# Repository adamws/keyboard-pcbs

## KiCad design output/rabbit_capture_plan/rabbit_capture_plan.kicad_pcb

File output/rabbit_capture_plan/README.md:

## rabbit_capture_plan/rabbit_capture_plan

[layout](rabbit_capture_plan-kle.json) - [PCB](rabbit_capture_plan.kicad_pcb)

{:loading="lazy"}

[Open in keyboard-layout-editor](http://www.keyboard-layout-editor.com/##@@_x:0.66&y:1.45&c=#777777;&=0,0&_c=#cccccc;&=0,1&_x:11.66;&=5,4&=5,5&=5,6&_c=#aaaaaa;&=5,7;&@_x:0.53&w:1.5;&=1,0&_c=#cccccc;&=1,1&_x:10.94;&=6,4&=6,5&=6,6&_x:0.37&c=#777777&w:1.25&h:2&w2:1.5&h2:1&x2:-0.25;&=6,7%0A%0A%0A0,0;&@_x:0.39&c=#aaaaaa&w:1.75;&=2,0&_c=#cccccc;&=2,1&_x:11.2;&=7,4&=7,5&=7,6%0A%0A%0A0,0;&@_x:0.25&c=#aaaaaa&w:2.25;&=3,0&_c=#cccccc;&=3,1&_x:10.47;&=8,4&=8,5&_c=#aaaaaa&w:1.75;&=8,6%0A%0A%0A1,0;&@_x:18&y:-0.7&c=#cccccc;&=9,0;&@_x:0.5&y:-0.3&c=#aaaaaa&w:1.25;&=4,0&_w:1.25;&=4,1;&@_x:17&y:-0.7&c=#cccccc;&=9,3&=9,4&=9,5;&@_r:8&x:2.97&y:-5.82;&=0,2&=0,3&=0,4&=0,5&=0,6;&@_x:3.47;&=1,2&=1,3&=1,4&=1,5&=1,6;&@_x:3.72;&=2,2&=2,3&=2,4&=2,5&=2,6;&@_x:4.22;&=3,2&=3,3&=3,4&=3,5;&@_x:4.72;&=4,2&_w:2;&=4,3&=4,4;&@_r:-8&x:9.87&y:-2.58;&=5,0&=5,1&=5,2&=5,3;&@_x:9.37;&=6,0&=6,1&=6,2&=6,3;&@_x:9.62;&=7,0&=7,1&=7,2&=7,3;&@_x:9.12;&=8,0&=8,1&=8,2&=8,3;&@_x:9.6&w:2.75;&=9,1&=9,2;&@_r:0&x:21.47&y:-5.9&c=#aaaaaa&w:1.5;&=6,7%0A%0A%0A0,1;&@_x:20.84&c=#777777&w:2.25;&=7,6%0A%0A%0A0,1;&@_x:20.72&c=#cccccc;&=8,6%0A%0A%0A1,1&=8,7%0A%0A%0A1,1)

{:loading="lazy"}

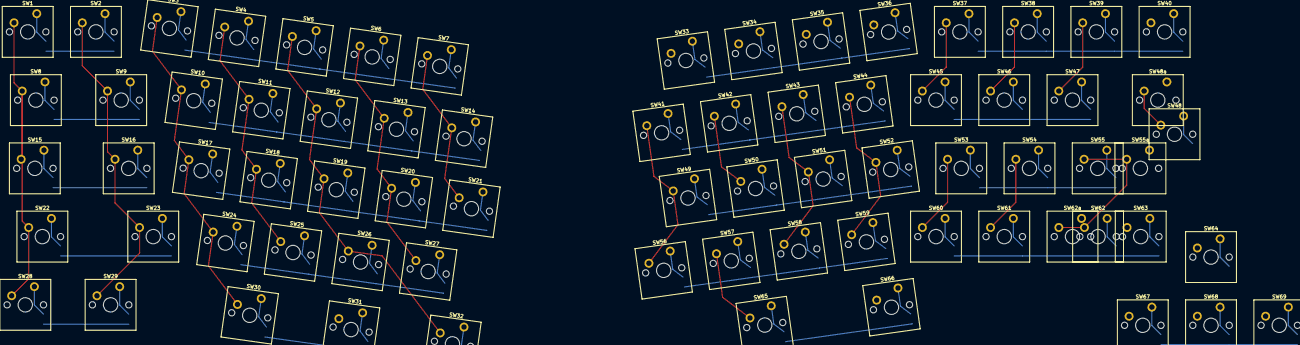
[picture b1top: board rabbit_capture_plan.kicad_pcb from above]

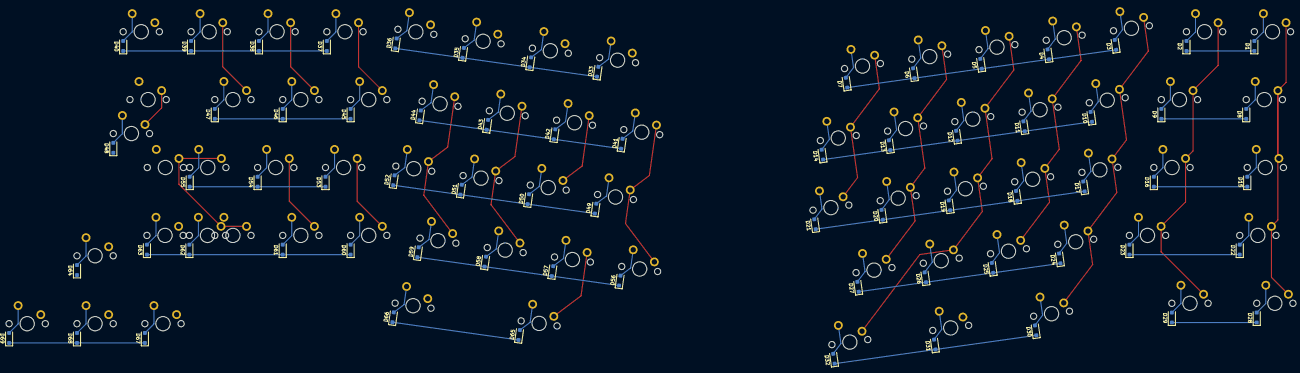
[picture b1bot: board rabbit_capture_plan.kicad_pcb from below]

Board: 2 copper layers, 141 parts (69 on the bottom side), 87 nets.

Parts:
D1, D2, D3, D4, D5, D6, D7, D8, D9, D10, D11, D12, D13, D14, D15, D16, D17, D18, D19, D20, D21, D22, D23, D24, D25, D26, D27, D28, D29, D30, D31, D32, D33, D34, D35, D36, D37, D38, D39, D40, D41, D42, D43, D44, D45, D46, D47, D48, D49, D50, D51, D52, D53, D54, D55, D56, D57, D58, D59, D60, D61, D62, D63, D64, D65, D66, D67, D68, D69: D_SOD-123F
SW1, SW2, SW3, SW4, SW5, SW6, SW7, SW8, SW9, SW10, SW11, SW12, SW13, SW14, SW15, SW16, SW17, SW18, SW19, SW20, SW21, SW22, SW23, SW24, SW25, SW26, SW27, SW28, SW29, SW30, SW31, SW32, SW33, SW34, SW35, SW36, SW37, SW38, SW39, SW40, SW41, SW42, SW43, SW44, SW45, SW46, SW47, SW48, SW48a, SW49, SW50, SW51, SW52, SW53, SW54, SW55, SW55a, SW56, SW57, SW58, SW59, SW60, SW61, SW62, SW62a, SW63, SW64, SW65, SW66, SW67, SW68, SW69: SW_Cherry_MX_PCB_1.00u

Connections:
COL0: SW1.1, SW8.1, SW15.1, SW22.1, SW28.1, SW33.1, SW41.1, SW49.1, SW56.1, SW64.1
COL1: SW2.1, SW9.1, SW16.1, SW23.1, SW29.1, SW34.1, SW42.1, SW50.1, SW57.1, SW65.1
COL2: SW3.1, SW10.1, SW17.1, SW24.1, SW30.1, SW35.1, SW43.1, SW51.1, SW58.1, SW66.1
COL3: SW4.1, SW11.1, SW18.1, SW25.1, SW31.1, SW36.1, SW44.1, SW52.1, SW59.1, SW67.1
COL4: SW5.1, SW12.1, SW19.1, SW26.1, SW32.1, SW37.1, SW45.1, SW53.1, SW60.1, SW68.1
COL5: SW6.1, SW13.1, SW20.1, SW27.1, SW38.1, SW46.1, SW54.1, SW61.1, SW69.1
COL6: SW7.1, SW14.1, SW21.1, SW39.1, SW47.1, SW55.1, SW55a.1, SW62.1, SW62a.1
COL7: SW40.1, SW48.1, SW48a.1, SW63.1
unnamed: D1.2, SW1.2
unnamed: D2.2, SW2.2
unnamed: D3.2, SW3.2
unnamed: D4.2, SW4.2
unnamed: D5.2, SW5.2
unnamed: D6.2, SW6.2
unnamed: D7.2, SW7.2
unnamed: D8.2, SW8.2
unnamed: D9.2, SW9.2
unnamed: D10.2, SW10.2
unnamed: D11.2, SW11.2
unnamed: D12.2, SW12.2
unnamed: D13.2, SW13.2
unnamed: D14.2, SW14.2
unnamed: D15.2, SW15.2
unnamed: D16.2, SW16.2
unnamed: D17.2, SW17.2
unnamed: D18.2, SW18.2
unnamed: D19.2, SW19.2
unnamed: D20.2, SW20.2
unnamed: D21.2, SW21.2
unnamed: D22.2, SW22.2
unnamed: D23.2, SW23.2
unnamed: D24.2, SW24.2
unnamed: D25.2, SW25.2
unnamed: D26.2, SW26.2
unnamed: D27.2, SW27.2
unnamed: D28.2, SW28.2
unnamed: D29.2, SW29.2
unnamed: D30.2, SW30.2
unnamed: D31.2, SW31.2
unnamed: D32.2, SW32.2
unnamed: D33.2, SW33.2
unnamed: D34.2, SW34.2
unnamed: D35.2, SW35.2
unnamed: D36.2, SW36.2
unnamed: D37.2, SW37.2
unnamed: D38.2, SW38.2
unnamed: D39.2, SW39.2
unnamed: D40.2, SW40.2
unnamed: D41.2, SW41.2
unnamed: D42.2, SW42.2
unnamed: D43.2, SW43.2
unnamed: D44.2, SW44.2
unnamed: D45.2, SW45.2
unnamed: D46.2, SW46.2
unnamed: D47.2, SW47.2
unnamed: D48.2, SW48.2, SW48a.2
unnamed: D49.2, SW49.2
unnamed: D50.2, SW50.2
unnamed: D51.2, SW51.2
unnamed: D52.2, SW52.2
unnamed: D53.2, SW53.2
unnamed: D54.2, SW54.2
unnamed: D55.2, SW55.2, SW55a.2
unnamed: D56.2, SW56.2
unnamed: D57.2, SW57.2
unnamed: D58.2, SW58.2
unnamed: D59.2, SW59.2
unnamed: D60.2, SW60.2
unnamed: D61.2, SW61.2
unnamed: D62.2, SW62.2, SW62a.2
unnamed: D63.2, SW63.2
unnamed: D64.2, SW64.2
unnamed: D65.2, SW65.2
unnamed: D66.2, SW66.2
unnamed: D67.2, SW67.2
unnamed: D68.2, SW68.2
unnamed: D69.2, SW69.2
ROW0: D1.1, D2.1, D3.1, D4.1, D5.1, D6.1, D7.1
ROW1: D8.1, D9.1, D10.1, D11.1, D12.1, D13.1, D14.1
ROW2: D15.1, D16.1, D17.1, D18.1, D19.1, D20.1, D21.1
ROW3: D22.1, D23.1, D24.1, D25.1, D26.1, D27.1
ROW4: D28.1, D29.1, D30.1, D31.1, D32.1
ROW5: D33.1, D34.1, D35.1, D36.1, D37.1, D38.1, D39.1, D40.1
ROW6: D41.1, D42.1, D43.1, D44.1, D45.1, D46.1, D47.1, D48.1
ROW7: D49.1, D50.1, D51.1, D52.1, D53.1, D54.1, D55.1
ROW8: D56.1, D57.1, D58.1, D59.1, D60.1, D61.1, D62.1, D63.1
ROW9: D64.1, D65.1, D66.1, D67.1, D68.1, D69.1
